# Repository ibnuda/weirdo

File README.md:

# Weirdo

It's a split keyboard that uses 1 Promicro (or its clone) and RJ45.

## Why?

Just because

## Does It Work?

Of course it works.

## Firmware?

It uses [QMK](https://qmk.fm) as the firmware.

## Keymaps?

Default: [default](https://github.com/ibnuda/qmk_firmware/tree/weirdo/keyboards/weirdo/keymaps/default)

[Denny Tom's Chording Engine](https://github.com/qmk/qmk_firmware/tree/master/users/dennytom/chording_engine):
[rick's combo](https://github.com/ibnuda/qmk_firmware/tree/weirdo/keyboards/weirdo/keymaps/rick-combo)

## License

GPLv3

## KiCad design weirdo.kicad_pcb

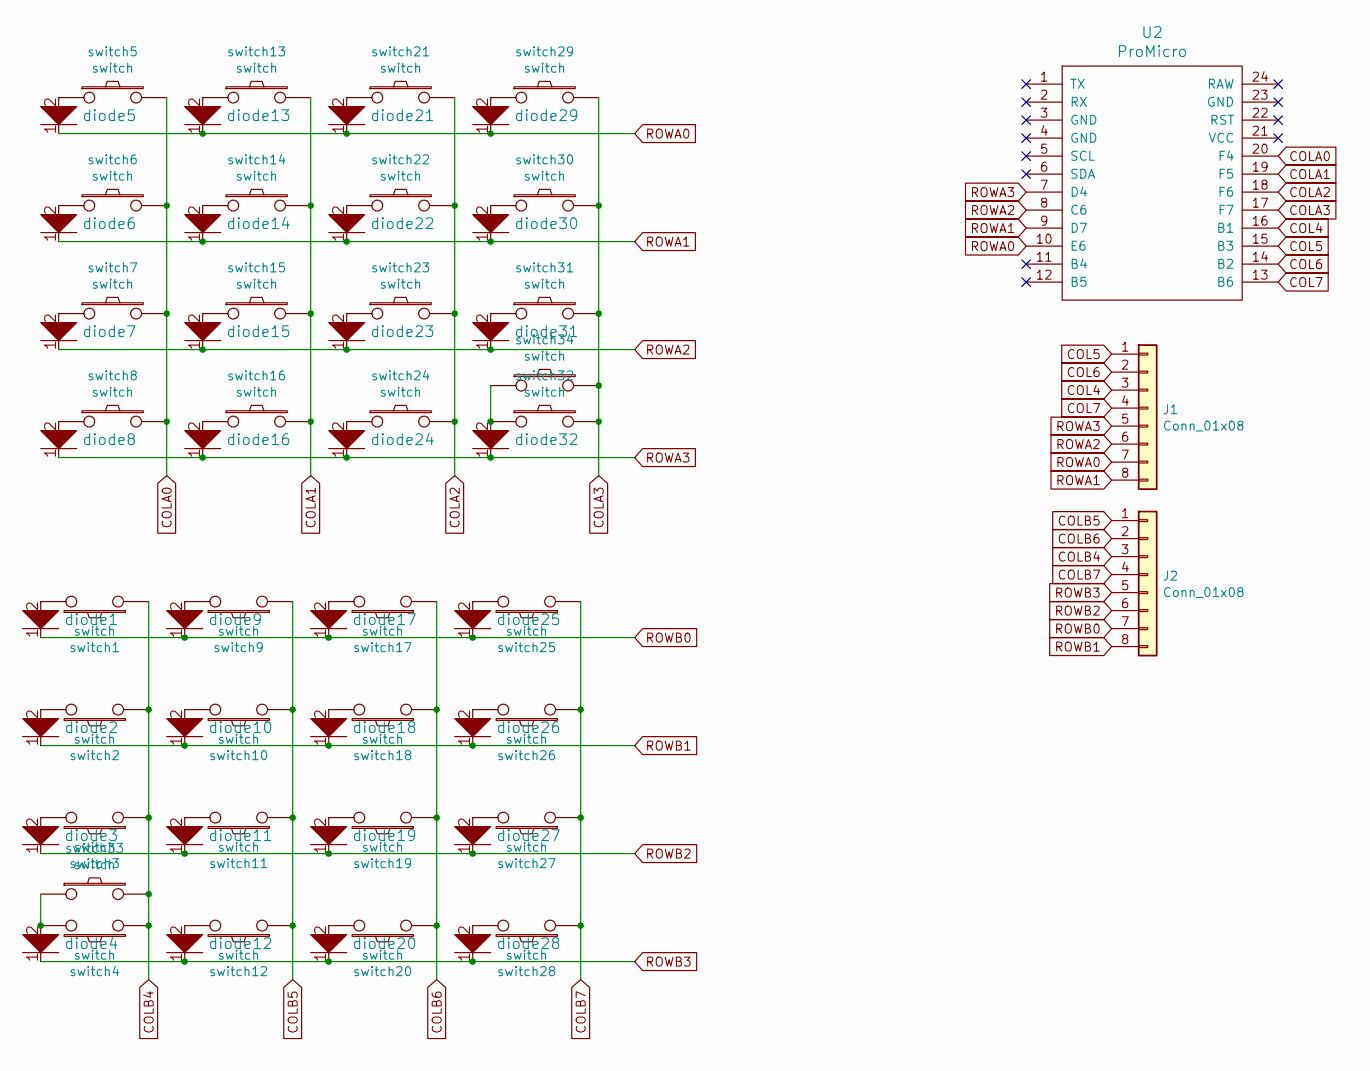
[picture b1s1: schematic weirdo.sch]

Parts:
J1, J2: Conn_01x08; RJ45_Ninigi_GE
U2: ProMicro; promicro
diode1, diode2, diode3, diode4, diode5, diode6, diode7, diode8, diode9, diode10, diode11, diode12, diode13, diode14, diode15, diode16, diode17, diode18, diode19, diode20, diode21, diode22, diode23, diode24, diode25, diode26, diode27, diode28, diode29, diode30, diode31, diode32: diode
switch1, switch2, switch3, switch5, switch6, switch7, switch8, switch9, switch10, switch11, switch12, switch13, switch14, switch15, switch16, switch17, switch18, switch19, switch20, switch21, switch22, switch23, switch24, switch25, switch26, switch27, switch28, switch29, switch30, switch31, switch33, switch34: switch; 1u-single
switch4, switch32: switch; 2u-single

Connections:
COL4: J1.3, U2.16 (B1)
COL5: J1.1, U2.15 (B3)
COL6: J1.2, U2.14 (B2)
COL7: J1.4, U2.13 (B6)
COLA0: U2.20 (F4), switch5.2, switch6.2, switch7.2, switch8.2
COLA1: U2.19 (F5), switch13.2, switch14.2, switch15.2, switch16.2
COLA2: U2.18 (F6), switch21.2, switch22.2, switch23.2, switch24.2
COLA3: U2.17 (F7), switch29.2, switch30.2, switch31.2, switch32.2, switch34.2
COLB4: J2.3, switch1.1, switch2.1, switch3.1, switch4.1, switch33.2
COLB5: J2.1, switch9.1, switch10.1, switch11.1, switch12.1
COLB6: J2.2, switch17.1, switch18.1, switch19.1, switch20.1
COLB7: J2.4, switch25.1, switch26.1, switch27.1, switch28.1
unnamed: diode1.2, switch1.2
unnamed: diode2.2, switch2.2
unnamed: diode3.2, switch3.2
unnamed: diode4.2, switch4.2, switch33.1
unnamed: diode5.2, switch5.1
unnamed: diode6.2, switch6.1
unnamed: diode7.2, switch7.1
unnamed: diode8.2, switch8.1
unnamed: diode9.2, switch9.2
unnamed: diode10.2, switch10.2
unnamed: diode11.2, switch11.2
unnamed: diode12.2, switch12.2
unnamed: diode13.2, switch13.1
unnamed: diode14.2, switch14.1
unnamed: diode15.2, switch15.1
unnamed: diode16.2, switch16.1
unnamed: diode17.2, switch17.2
unnamed: diode18.2, switch18.2
unnamed: diode19.2, switch19.2
unnamed: diode20.2, switch20.2
unnamed: diode21.2, switch21.1
unnamed: diode22.2, switch22.1
unnamed: diode23.2, switch23.1
unnamed: diode24.2, switch24.1
unnamed: diode25.2, switch25.2
unnamed: diode26.2, switch26.2
unnamed: diode27.2, switch27.2
unnamed: diode28.2, switch28.2
unnamed: diode29.2, switch29.1
unnamed: diode30.2, switch30.1
unnamed: diode31.2, switch31.1
unnamed: diode32.2, switch32.1, switch34.1
ROWA0: J1.7, U2.10 (E6), diode5.1, diode13.1, diode21.1, diode29.1
ROWA1: J1.8, U2.9 (D7), diode6.1, diode14.1, diode22.1, diode30.1
ROWA2: J1.6, U2.8 (C6), diode7.1, diode15.1, diode23.1, diode31.1
ROWA3: J1.5, U2.7 (D4), diode8.1, diode16.1, diode24.1, diode32.1
ROWB0: J2.7, diode1.1, diode9.1, diode17.1, diode25.1
ROWB1: J2.8, diode2.1, diode10.1, diode18.1, diode26.1
ROWB2: J2.6, diode3.1, diode11.1, diode19.1, diode27.1
ROWB3: J2.5, diode4.1, diode12.1, diode20.1, diode28.1

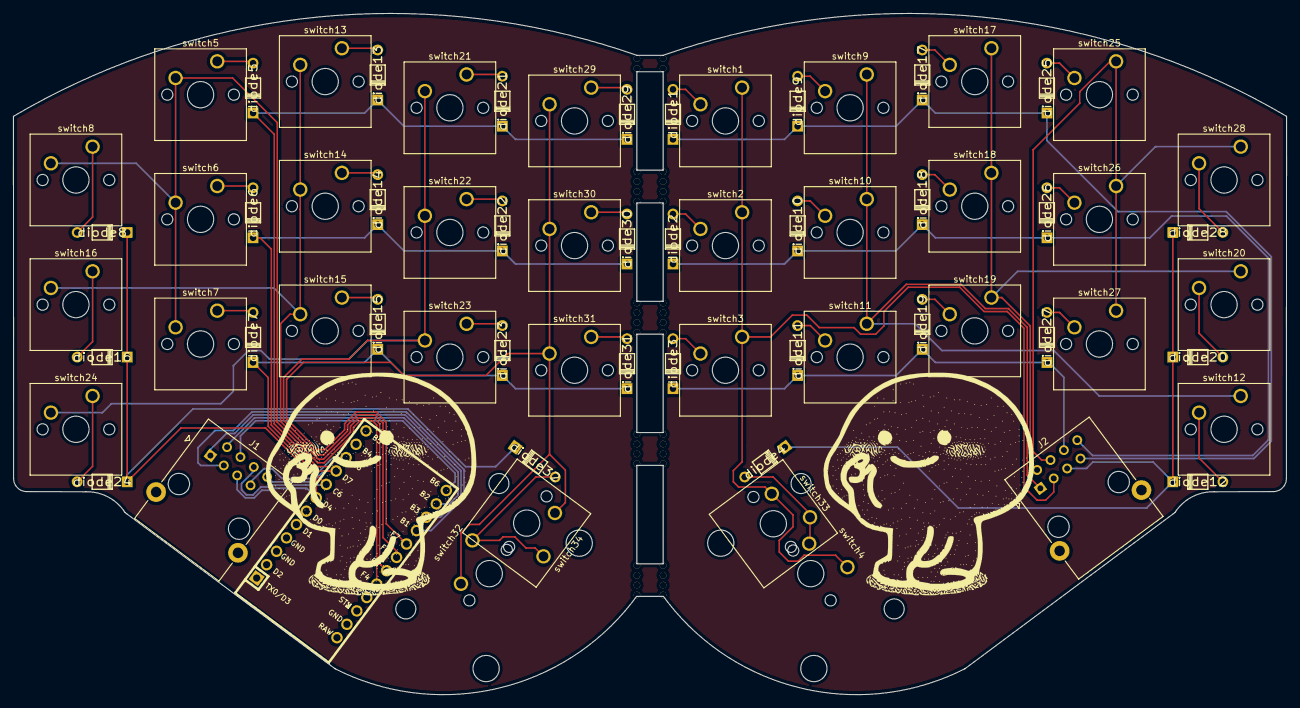
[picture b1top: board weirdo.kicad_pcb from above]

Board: 2 copper layers, 194.0 x 103.8 mm, 87 parts (1 on the bottom side), 52 nets.

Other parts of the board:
Ref**: Val**; holes_two
Ref**#2, Ref**#3, Ref**#4, Ref**#5, Ref**#6, Ref**#7, Ref**#8, Ref**#9, Ref**#10, Ref**#11, Ref**#12, Ref**#13, Ref**#14, Ref**#15, Ref**#16, Ref**#17, Ref**#18: Val**; holes_two

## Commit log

2020-07-09 weirdos of the world, unite!
2020-07-10 hoah.
2020-07-11 cases.
2020-08-14 added `readme.md` and pics so you know what you see.
